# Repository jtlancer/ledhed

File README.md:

##Snoozerly Dawn Simulator
An Arduino-controlled combination [Ok to Wake](http://www.amazon.com/s/ref=nb_sb_noss?url=search-alias%3Daps&field-keywords=child%20ok%20to%20wake) alarm clock, [dawn simulator](http://www.amazon.com/Sunrise-Therapy-Light-Dawn-Simulator/dp/B0010AX7UY), and [PWM driver](http://www.amazon.com/LEDwholesalers-Dimming-Controller-LED-Lights/dp/B003L4KKF2/ref=pd_sim_hg_5).

###Components
* [16 ft Hitlits warm white LED strip light](http://www.amazon.com/Hitlights-Flexible-Ribbon-Adapter-included/dp/B005GL5UG2/ref=sr_1_sc_1?ie=UTF8&qid=1389329143&sr=8-1-spell&keywords=hitlits+led+strip) ([data sheet](http://www.hitlights.com/ls3528-30-group.html)) 
* ATmega328p
* [Maxim DS1388 RTC](http://www.digikey.com/product-detail/en/DS1388Z-33%2BT%26R/DS1388Z-33%2BT%26RCT-ND/4146799)
* [Nokia 5110 LCD module](http://www.ebay.com/bhp/nokia-5110)
* [Atmel AT42QT1070 capacitive touch sensor](http://www.digikey.com/product-detail/en/AT42QT1070-SSU%20QS529/AT42QT1070-SSU%20QS529CT-ND/2637953)

###Libraries in Repository

* [DS1307 RTC](https://github.com/adafruit/RTClib) Arduino library modified for the DS1388.

###Other Libraries
* [Eagle parts](https://github.com/jtlancer/jt_parts) customized from [Sparkfun](https://github.com/sparkfun/SparkFun-Eagle-Libraries) and [Adafruit](https://github.com/adafruit/Adafruit-Eagle-Library).
* Adafruit [PCD8544 Nokia 5110](https://github.com/adafruit/Adafruit-PCD8544-Nokia-5110-LCD-library) Arduino library.

##More Info
[crispytater.com](http://blog-crispytater.rhcloud.com/snoozerly-project/)

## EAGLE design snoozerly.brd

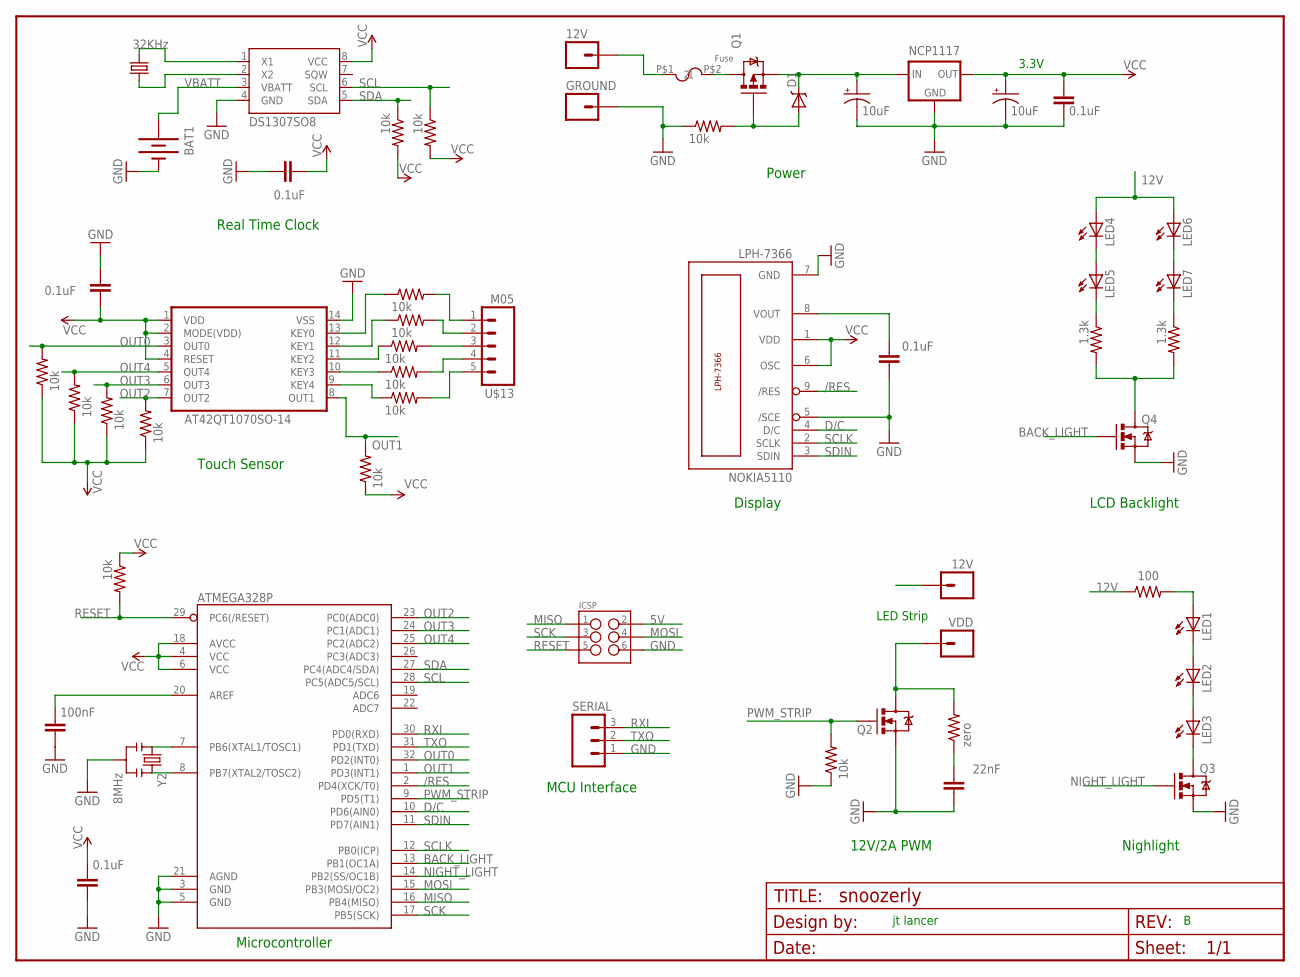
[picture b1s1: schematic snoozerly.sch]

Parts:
12V: M01; M01_BIGHOLE
AT42QT1070: AT42QT1070SO-14; SO-14
BAT1: BATTERY12MM; BATTCON_12MM
C1: 100nF; 0805
C2, C3, C6, C8, C9: 0.1uF; 0805
C4: 22nF; 0805
C5, C7: 10uF; CAP-PANASONIC-C
D1: DIODE-SCHOTTKYDO-214AA; DO-214AA
GROUND: M01; M01_BIGHOLE
ICSP: M03X2POGO_PINS; 2X3_POGO
LED1, LED2, LED3: LED; SIDEVIEW-LED
LED4, LED5, LED6, LED7: LED0603; LED-0603
NCP1117: VREG-3.3VNCP1117; TO-252
NOKIA5110: LPH-7366; NOKIA5110
Q1: MOSFET_PCHANNEL; DPAK
Q2: MOSFET-NCHANNELFDD8780; DPAK@1
Q3, Q4: MOSFET-NCHANNELBSS123LT1G; SOT23
SERIAL: M031X03_NO_SILK; 1X03_NO_SILK
U1: ATMEGA328P; TQFP32-08
U$1: FRAME_LETTER; CREATIVE_COMMONS
U$2, U$4, U$5, U$14, U$15: 10k; RESISTOR-0805
U$3: DS1307SO8; SO08
U$6, U$7, U$8, U$9, U$10, U$11, U$21, U$22, U$23, U$24: 10k; R0603
U$12: Fuse; FUSE-LITTLE-251
U$13: M05; M05-SMD
U$16: 100; RESISTOR-0805
U$17, U$18: 1.3k; RESISTOR-0805
U$25: zero; R0603
U$26: VDD; M01_BIGHOLE
U$27: 12V; M01_BIGHOLE
Y1: 32KHz; CRYSTAL-32KHZ-SMD
Y2: 8MHz; RESONATOR-SMD

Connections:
5V: AT42QT1070.1 (VDD), AT42QT1070.2 (MODE(VDD)), AT42QT1070.4 (RESET), C2.1, C3.1, C7.+, C8.1, C9.1, ICSP.P$2 (2), NCP1117.2 (OUT), NOKIA5110.1 (VDD), NOKIA5110.6 (OSC), U1.4 (VCC), U1.6 (VCC), U1.18 (AVCC), U$2.1, U$3.8 (VCC), U$4.2, U$5.2, U$6.1, U$21.1, U$22.1, U$23.1, U$24.1
12V: C5.+, D1.C, LED4.A, LED6.A, NCP1117.3 (IN), Q1.3 (S), U$16.1, U$27.1
/RES: NOKIA5110.9 (/RES), U1.2 (PD4(XCK/T0))
BACK_LIGHT: Q4.1 (G), U1.13 (PB1(OC1A))
D/C: NOKIA5110.4 (D/C), U1.10 (PD6(AIN0))
GND: AT42QT1070.14 (VSS), BAT1.GND (-), C1.2, C2.2, C3.2, C4.1, C5.-, C6.1, C7.-, C8.2, C9.2, GROUND.1, ICSP.P$6 (6), NCP1117.1 (GND), NOKIA5110.5 (/SCE), NOKIA5110.7 (GND), Q2.3 (S), Q3.2 (S), Q4.2 (S), SERIAL.1, U1.3 (GND), U1.5 (GND), U1.21 (AGND), U$3.4 (GND), U$14.1, U$15.1, Y2.2
KEY0: AT42QT1070.13 (KEY0), U$7.1
KEY1: AT42QT1070.12 (KEY1), U$8.1
KEY2: AT42QT1070.11 (KEY2), U$9.1
KEY3: AT42QT1070.10 (KEY3), U$10.1
KEY4: AT42QT1070.9 (KEY4), U$11.1
MISO: ICSP.P$1 (1), U1.16 (PB4(MISO))
MOSI: ICSP.P$4 (4), U1.15 (PB3(MOSI/OC2))
unnamed: U1.7 (PB6(XTAL1/TOSC1)), Y2.1
unnamed: LED7.C, U$18.1
unnamed: U1.8 (PB7(XTAL2/TOSC2)), Y2.3
unnamed: LED4.C, LED5.A
unnamed: U$3.1 (X1), Y1.X2 (2)
unnamed: U$3.2 (X2), Y1.X1 (1)
unnamed: 12V.1, U$12.P$1 (1)
unnamed: LED5.C, U$17.1
unnamed: Q4.3 (D), U$17.2, U$18.2
unnamed: C1.1, U1.20 (AREF)
unnamed: LED1.P$1 (A), U$16.2
unnamed: Q1.4 (D), U$12.P$2 (2)
unnamed: Q2.4 (D), U$25.2, U$26.1
unnamed: LED1.P$2 (C), LED2.P$1 (A)
unnamed: D1.A, Q1.1 (G), U$14.2
unnamed: LED6.C, LED7.A
unnamed: C4.2, U$25.1
unnamed: U$9.2, U$13.3
unnamed: C6.2, NOKIA5110.8 (VOUT)
unnamed: U$11.2, U$13.5
unnamed: LED2.P$2 (C), LED3.P$1 (A)
unnamed: U$10.2, U$13.4
unnamed: U$8.2, U$13.2
unnamed: U$7.2, U$13.1
unnamed: LED3.P$2 (C), Q3.3 (D)
NIGHT_LIGHT: Q3.1 (G), U1.14 (PB2(SS/OC1B))
OUT0: AT42QT1070.3 (OUT0), U1.32 (PD2(INT0)), U$6.2
OUT1: AT42QT1070.8 (OUT1), U1.1 (PD3(INT1)), U$23.2
OUT2: AT42QT1070.7 (OUT2), U1.23 (PC0(ADC0)), U$22.2
OUT3: AT42QT1070.6 (OUT3), U1.24 (PC1(ADC1)), U$21.2
OUT4: AT42QT1070.5 (OUT4), U1.25 (PC2(ADC2)), U$24.2
PWM_STRIP: Q2.1 (G), U1.9 (PD5(T1)), U$15.2
RESET: ICSP.P$5 (5), U1.29 (PC6(/RESET)), U$2.2
RXI: SERIAL.3, U1.30 (PD0(RXD))
SCK: ICSP.P$3 (3), U1.17 (PB5(SCK))
SCL: U1.28 (PC5(ADC5/SCL)), U$3.6 (SCL), U$5.1
SCLK: NOKIA5110.2 (SCLK), U1.12 (PB0(ICP))
SDA: U1.27 (PC4(ADC4/SDA)), U$3.5 (SDA), U$4.1
SDIN: NOKIA5110.3 (SDIN), U1.11 (PD7(AIN1))
TXO: SERIAL.2, U1.31 (PD1(TXD))
VBATT: BAT1.PWR@1 (+), U$3.3 (VBATT)

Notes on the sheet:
jt lancer
Real Time Clock
Touch Sensor
Microcontroller
MCU Interface
12V/2A PWM
Nighlight
LCD Backlight
Display
Power
3.3V
LED Strip

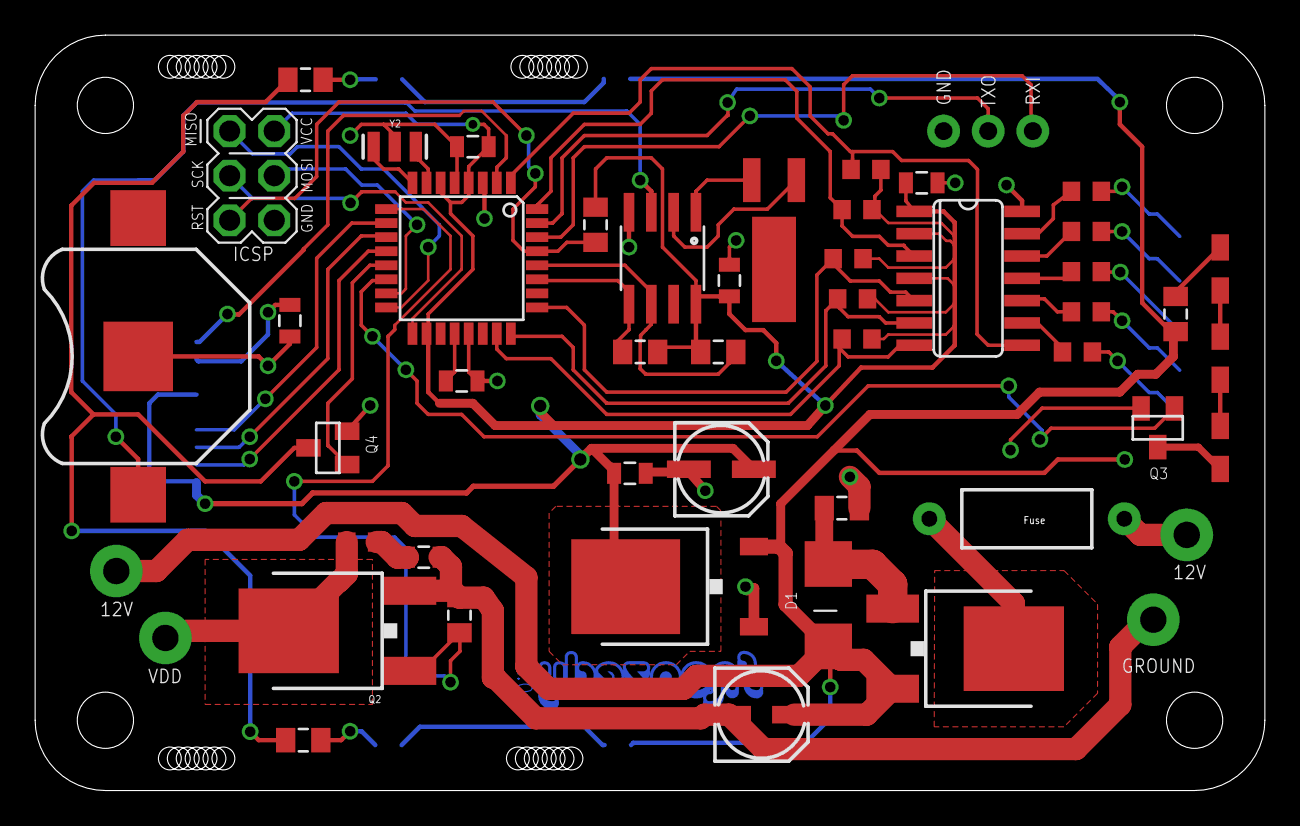
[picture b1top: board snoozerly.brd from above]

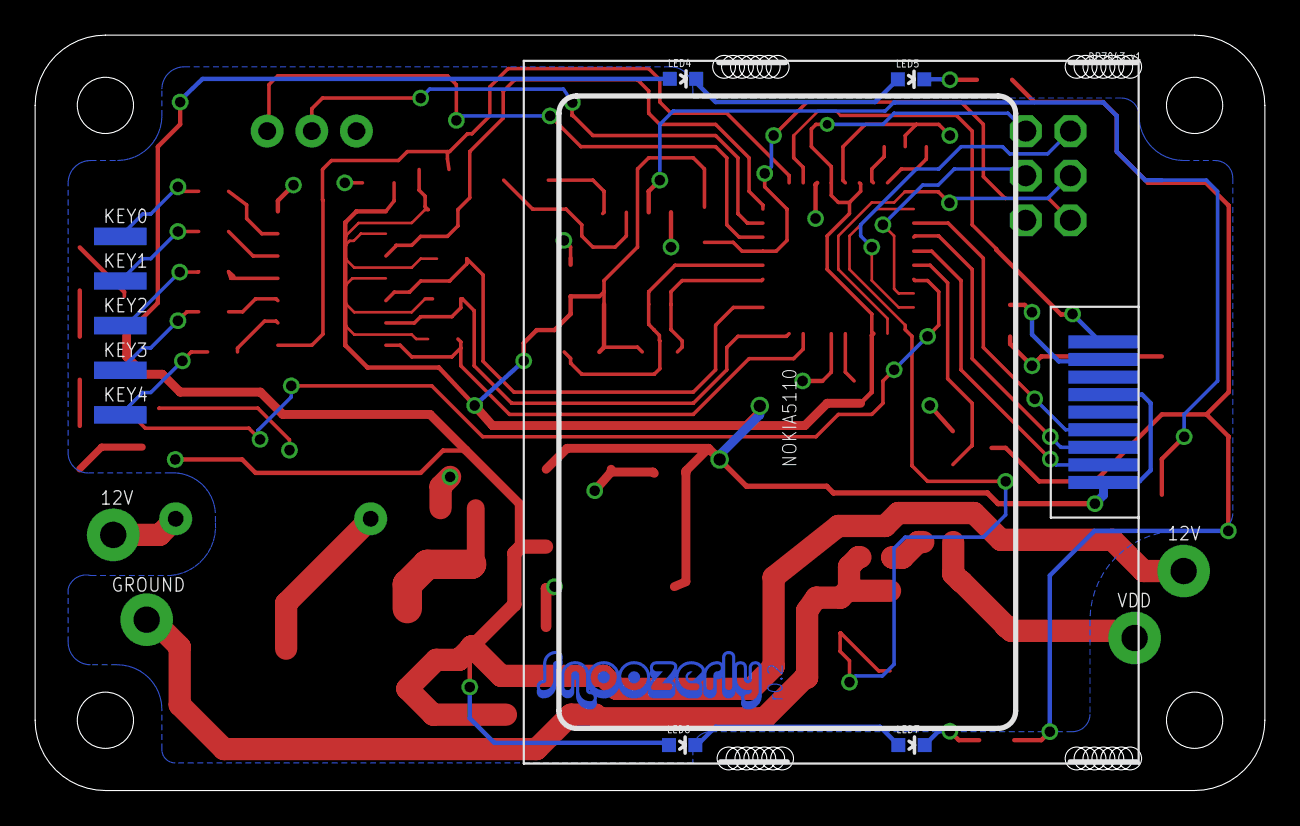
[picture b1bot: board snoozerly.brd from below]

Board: 2 copper layers, 70.0 x 43.0 mm, 59 parts (7 on the bottom side), 54 nets.

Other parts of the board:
U$19: SNOOZERLY_TOP
U$20: DP7043_V1

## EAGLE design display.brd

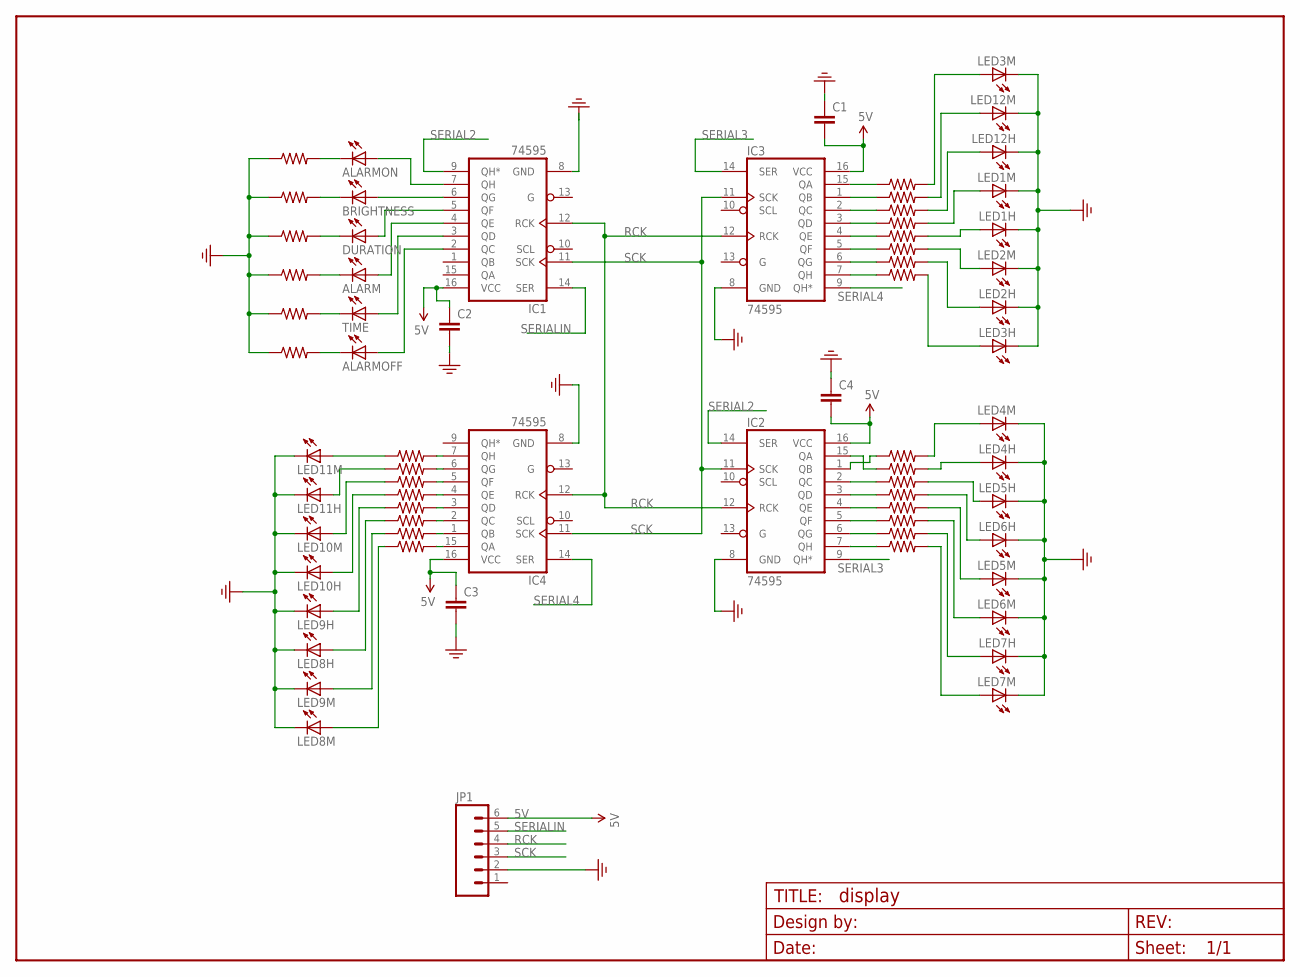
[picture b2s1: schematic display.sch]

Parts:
ALARM: LED1206; LED-1206
ALARMOFF: LED1206; LED-1206
ALARMON: LED1206; LED-1206
BRIGHTNESS: LED1206; LED-1206
C1, C2, C3, C4: CAP0805; 0805
DURATION: LED1206; LED-1206
FRAME1: FRAME-LETTER; CREATIVE_COMMONS
IC1, IC2, IC3, IC4: 74595; TSSOP16
JP1: M06SIP; 1X06
LED1H, LED1M, LED2H, LED2M, LED3H, LED3M, LED4H, LED4M, LED5H, LED5M, LED6H, LED6M, LED7H, LED7M, LED8H, LED8M, LED9H, LED9M, LED10H, LED10M, LED11H, LED11M, LED12H, LED12M: LED1206; LED-1206
TIME: LED1206; LED-1206
U$2, U$3, U$6, U$7, U$8, U$9, U$10, U$11, U$12, U$13, U$14, U$15, U$16, U$17, U$18, U$19, U$20, U$21, U$22, U$23, U$24, U$25, U$26, U$27, U$28, U$29, U$30, U$31, U$32, U$33: RESISTOR; RESISTOR-0805

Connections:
5V: C1.2, C2.1, C3.1, C4.2, IC1.16 (VCC), IC2.16 (VCC), IC3.16 (VCC), IC4.16 (VCC), JP1.6
GND: C1.1, C2.2, C3.2, C4.1, IC1.8 (GND), IC2.8 (GND), IC3.8 (GND), IC4.8 (GND), JP1.2, LED1H.C, LED1M.C, LED2H.C, LED2M.C, LED3H.C, LED3M.C, LED4H.C, LED4M.C, LED5H.C, LED5M.C, LED6H.C, LED6M.C, LED7H.C, LED7M.C, LED8H.C, LED8M.C, LED9H.C, LED9M.C, LED10H.C, LED10M.C, LED11H.C, LED11M.C, LED12H.C, LED12M.C, U$24.1, U$25.1, U$30.1, U$31.1, U$32.1, U$33.1
unnamed: LED12H.A, U$8.2
unnamed: LED12M.A, U$7.2
unnamed: LED1M.A, U$9.2
unnamed: LED1H.A, U$10.2
unnamed: LED2M.A, U$11.2
unnamed: LED3H.A, U$12.2
unnamed: LED2H.A, U$13.2
unnamed: LED3M.A, U$6.2
unnamed: IC2.2 (QC), U$22.1
unnamed: IC2.3 (QD), U$23.1
unnamed: IC2.4 (QE), U$26.1
unnamed: IC2.5 (QF), U$27.1
unnamed: IC2.15 (QA), U$21.1
unnamed: IC3.15 (QA), U$6.1
unnamed: LED4M.A, U$20.2
unnamed: IC2.1 (QB), U$20.1
unnamed: LED11M.A, U$18.1
unnamed: LED11H.A, U$17.1
unnamed: LED10M.A, U$16.1
unnamed: LED10H.A, U$19.1
unnamed: LED9H.A, U$15.1
unnamed: LED8H.A, U$14.1
unnamed: LED4H.A, U$21.2
unnamed: LED9M.A, U$3.1
unnamed: IC2.6 (QG), U$28.1
unnamed: IC2.7 (QH), U$29.1
unnamed: LED8M.A, U$2.1
unnamed: LED5H.A, U$22.2
unnamed: IC4.1 (QB), U$3.2
unnamed: IC4.15 (QA), U$2.2
unnamed: IC3.1 (QB), U$7.1
unnamed: IC3.2 (QC), U$8.1
unnamed: IC3.3 (QD), U$9.1
unnamed: IC3.4 (QE), U$10.1
unnamed: IC3.5 (QF), U$11.1
unnamed: IC3.6 (QG), U$13.1
unnamed: IC3.7 (QH), U$12.1
unnamed: IC4.7 (QH), U$18.2
unnamed: IC4.6 (QG), U$17.2
unnamed: IC4.5 (QF), U$16.2
unnamed: IC4.3 (QD), U$15.2
unnamed: IC4.2 (QC), U$14.2
unnamed: IC4.4 (QE), U$19.2
unnamed: LED6H.A, U$23.2
unnamed: LED5M.A, U$26.2
unnamed: LED6M.A, U$27.2
unnamed: LED7H.A, U$28.2
unnamed: LED7M.A, U$29.2
unnamed: ALARMON.A, IC1.7 (QH)
unnamed: BRIGHTNESS.A, IC1.6 (QG)
unnamed: ALARM.A, IC1.4 (QE)
unnamed: IC1.3 (QD), TIME.A
unnamed: ALARMOFF.A, IC1.2 (QC)
unnamed: ALARMOFF.C, U$33.2
unnamed: TIME.C, U$32.2
unnamed: ALARM.C, U$31.2
unnamed: DURATION.C, U$30.2
unnamed: BRIGHTNESS.C, U$25.2
unnamed: ALARMON.C, U$24.2
unnamed: DURATION.A, IC1.5 (QF)
RCK: IC1.12 (RCK), IC2.12 (RCK), IC3.12 (RCK), IC4.12 (RCK), JP1.4
SCK: IC1.11 (SCK), IC2.11 (SCK), IC3.11 (SCK), IC4.11 (SCK), JP1.3
SERIAL2: IC1.9 (QH*), IC2.14 (SER)
SERIAL3: IC2.9 (QH*), IC3.14 (SER)
SERIAL4: IC3.9 (QH*), IC4.14 (SER)
SERIALIN: IC1.14 (SER), JP1.5

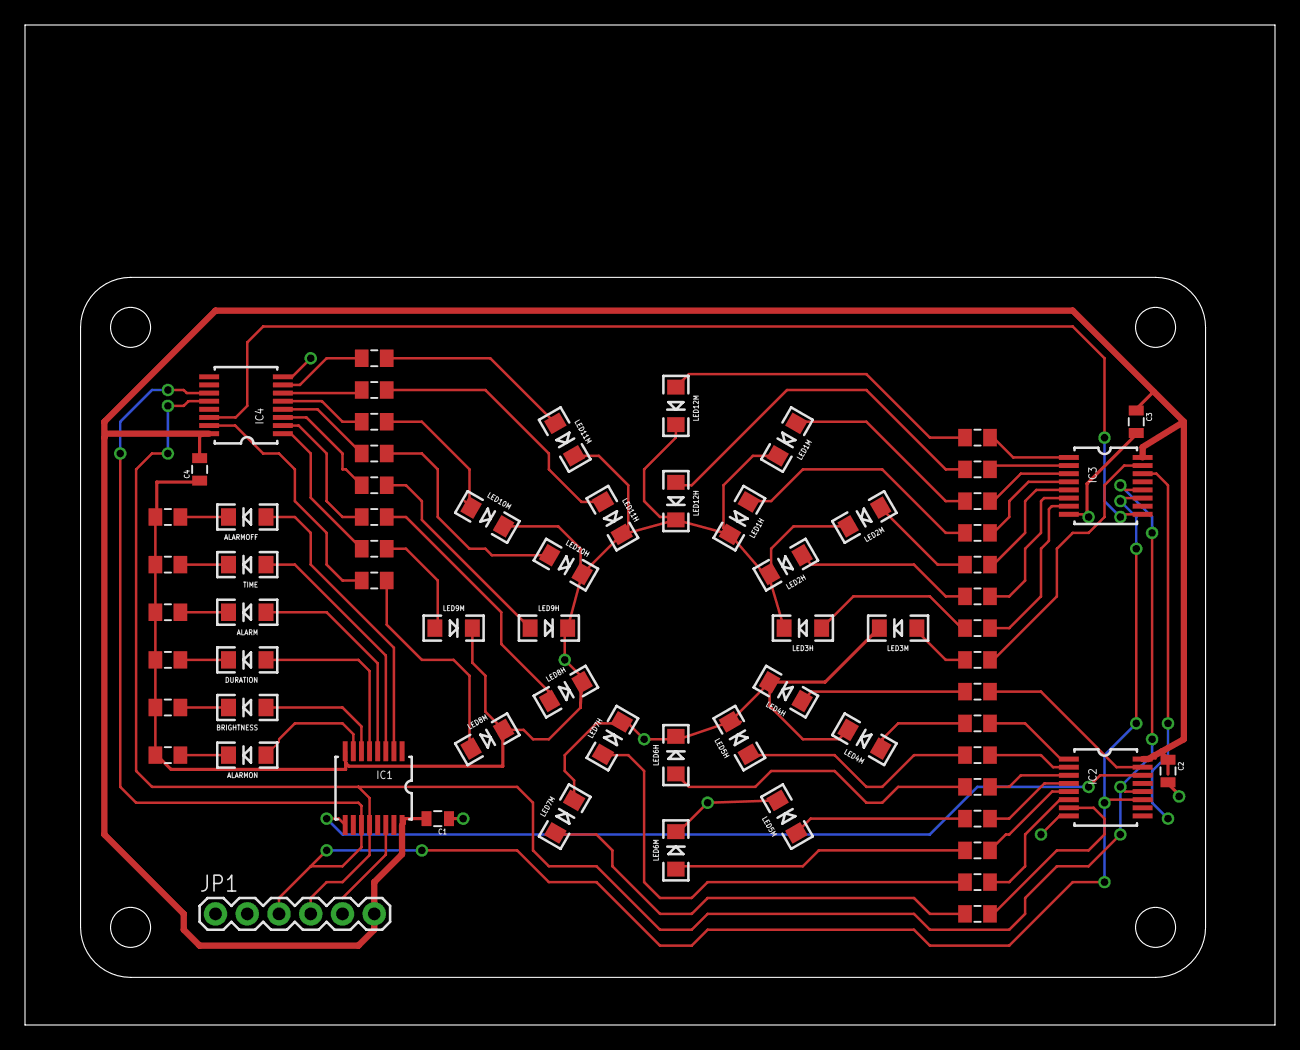
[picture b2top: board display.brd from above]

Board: 2 copper layers, 100.0 x 80.0 mm, 71 parts (0 on the bottom side), 68 nets.

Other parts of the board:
U$1: DP9056_V1

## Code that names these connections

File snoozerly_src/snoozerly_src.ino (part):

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byte nightlight_level = 0;

// map key pins to a standard order (top, bottom, left, right)
// touch sensor key0 = pin 2 = bottom 
// touch sensor key1 = pin 3 = top
// touch sensor key2 = pin 14 = left
// touch sensor key3 = pin 15 = right
// touch sensor key4 = unused
#define NUM_KEY_PINS 4
int my_key_pins[4] = {3, 2, 14, 15};
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
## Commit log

2013-08-24 begin placing components to check fit
2013-08-24 finished placing hour and minute leds
2013-08-24 initial routing attempt for 24min/hour leds. forgot resistors!
2013-08-25 added resistors. routed all leds.
2013-08-25 changed board to 90 x 56
2013-08-25 completed draft pcb layout for display board
2013-08-26 fixed twisted nets in display schematic
2013-08-26 Renamed controller > display. Removed resitor names. Added IC1 QH to IC2 serial.
2013-09-01 first commit with controller board. layed out power section.
2013-09-02 removed parts order from repo
2013-09-03 reoriented controller to match with display.
2013-09-03 fixed inconsistency between board and schematic.
2013-09-04 began layout of mcu section
2013-09-05 completed micro section schematic. split power from led strip pwm sections.
2013-09-05 completed RTC and micro schematic. to do: switches
2013-09-06 Beginning of new controller board layout.
2013-09-07 Layed out micro, jumpers, and rtc section.
2013-09-07 controller board layout complete.
2013-09-09 added fuse. tore up power traces.
2013-09-12 commit prior to adding reverse polarity protection.
2013-09-12 removed smaller board reference outline.
2013-09-13 began moving controller to smaller board size.
2013-09-18 added to do notes to schematic file.
2013-09-18 removed totem pole, switches, encoder, and disaply board jumper.
2013-09-23 changed to one board design.
    added LCD. added capacitive sense IC. changed to SMD programming
    header.
2013-09-26 Layed out new power section. Some new digital routing. Added rt angle SMT LEDs.
2013-09-27 added sense IC footprint and jumper. layed out "high" power section.
2013-09-28 made 12V traces narrower. modified nokia5110 package.
2013-09-29 decreased board size
    add backlight leds. changed to locking through hole programming header.
    reorganized and tightened voltage regulator section.
2013-10-03 added current limit resistors. tightened rtc-mcu spacing.
2013-10-05 wired lcd for software reset.
2013-10-07 added sideview led footprint and replaced for night lights.
2013-10-09 compacted layout. rerouted rtc. routed cap IC.
2013-10-10 put leds in series. continue to tweak layout.
2013-10-11 pre mod of power section
2013-10-11 new power section layout.
    added leds to 12v rail.
2013-10-12 all routing complete!
2013-10-12 added gerbers
2013-10-13 pre v0.1a branch
2013-10-13 added board documentation
2013-10-13 added logo and revision text to top layer
2013-10-14 updated ground plane with curves and cutouts.
2013-10-14 Added VCC test point and snoozerly graphic.
2013-10-16 added status and power connectors, and lcd drill holes.
2013-10-17 p-channel pad expanded
2013-10-17 renamed board and schematic files
2013-10-19 added output 0603 pullup resistors to touch sensor.
2013-10-19 Added electrolytics and snubber jumper.
2013-10-22 added top control board.
2013-10-25 updated diode and SO-14 footprint
2013-10-30 before remove daughter board
2013-10-31 before modifying vreg footprint
2013-10-31 updated vreg pinouts/footprint and rerouted traces
2013-10-31 update pchannel footprint and fixed spacings
2013-11-02 oshpark upload archive
2013-11-17 fixed air wire to led strip mosfet
2013-11-17 fixed touch sensor vcc and gnd. increased docu fonts.
2013-11-21 updates before touch sensor changes.
2013-11-21 increase drill size change remaining.
2013-11-27 increased 10uf cap pads
2013-12-16 directory cleanup
2013-12-24 added snoozerly arduino source. moved to dropbox.
2013-12-25 in process of building menu structure
2013-12-28 fixed issue with clearing temp time hour/minute when exiting adjust mode. before implementing save time.
2013-12-28 save new time function working.
2013-12-29 added leading zero to minute in display.
2013-12-30 implemented set and enable alarm.
2013-12-30 fixed minor issues
2014-01-09 updated sketch
2014-01-09 test commit
2014-01-10 removed image
2014-01-10 removed rules files
2014-01-10 added read me
2014-01-10 added schematic pdf and RTClib for DS1388
2014-01-10 updated board file. added board pdf.
2014-01-11 updated read me
2014-02-15 before changing input/output power pads/holes
2014-02-16 added big power holes
    rerouted traces around corners. put test/prog headers on 0.1" center
2014-02-18 complete rev 2 board for pcb order upload

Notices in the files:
parts and their libraries:
SparkFun-DigitalIC: Licensing: CC v3.0 Share-Alike You are welcome to use this library for commercial purposes.
SparkFun-Aesthetics: Released under the Creative Commons Attribution Share-Alike 3.0 License
SparkFun-Aesthetics: http://creativecommons.org/licenses/by-sa/3.0
